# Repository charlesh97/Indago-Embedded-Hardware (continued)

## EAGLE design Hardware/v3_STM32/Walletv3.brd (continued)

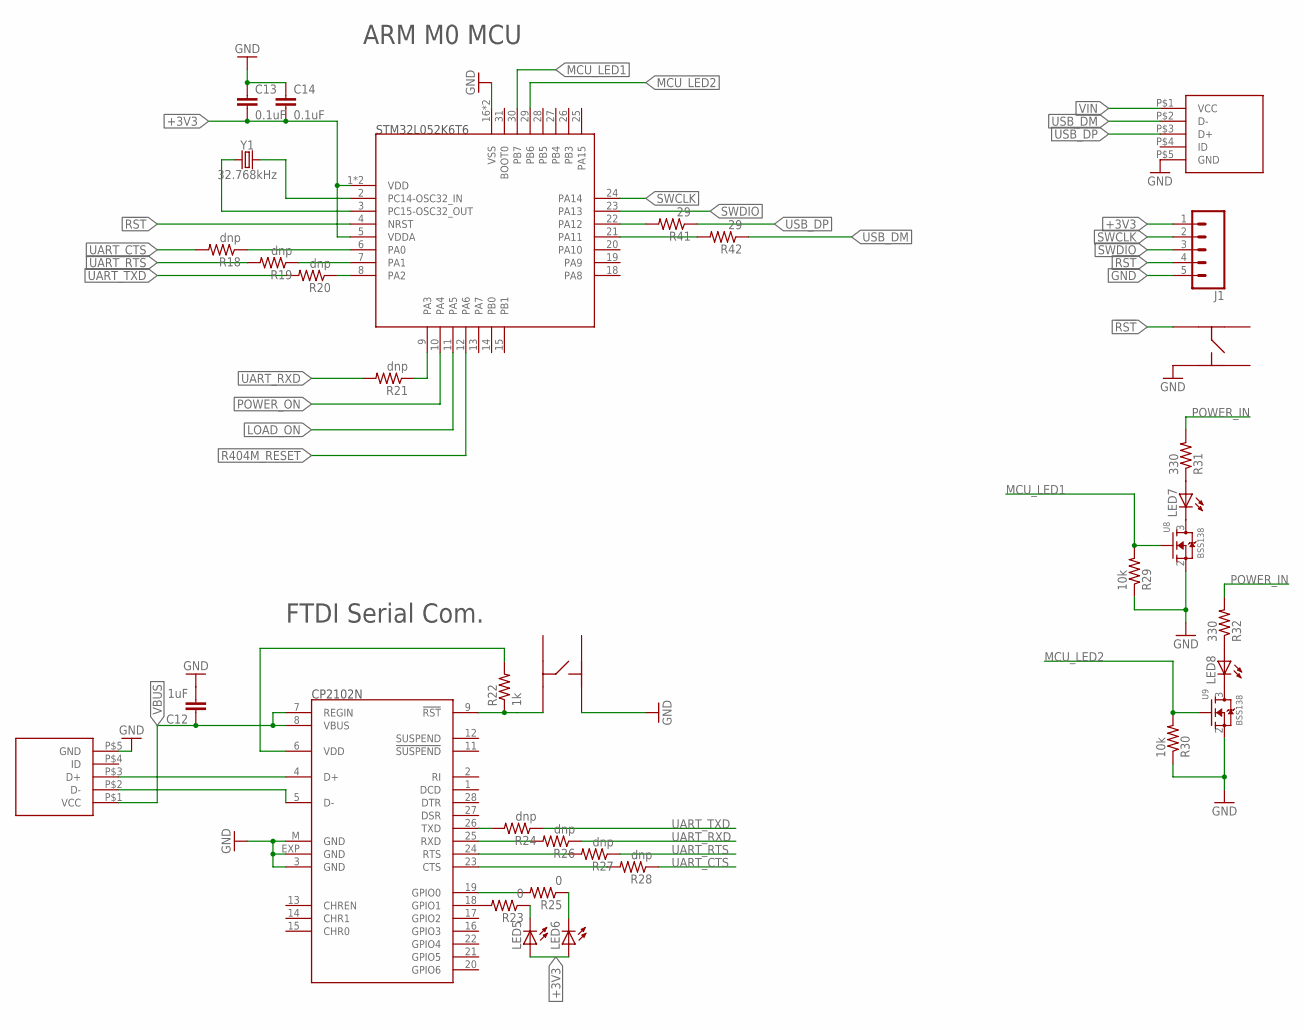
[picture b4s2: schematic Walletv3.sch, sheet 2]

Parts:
C12: 1uF; C0402
C13, C14: 0.1uF; C0402
IC1: CP2102; MLP28
J1: CONN_05; 1X05
LED5, LED6, LED7, LED8: LEDCHIPLED_0603; CHIPLED_0603
R18, R19, R20, R21, R24, R26, R27, R28: dnp; R0402
R22: 1k; R0402
R23, R25: 0; R0402
R29, R30: 10k; R0402
R31, R32: 330; R0402
R41, R42: 29; R0402
S3, S4: KMR731NG
U7: STM32L052K6T6LQFP32-7X7; QFP80P900X900X160-32
U8, U9: BSS138; SOT23-3
U$3, U$4: MICRO_USB; MOLEX_USB
Y1: 32.768kHz; CRYSTAL-SMD-3.2X1.5MM

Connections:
!RST: J1.4, S4.P$1, U7.4 (NRST)
+3V3: C13.2, C14.2, J1.1, LED5.A, LED6.A, U7.1 (VDD), U7.5 (VDDA), U7.17 (VDD); also elsewhere on the board
D_N: IC1.5 (D-), U$3.P$2 (D-)
D_P: IC1.4 (D+), U$3.P$3 (D+)
GND: C12.2, C13.1, C14.1, IC1.3 (GND), IC1.EXP (GND), IC1.M (GND), J1.5, R29.1, R30.1, S3.P$4, S4.P$4, U7.16 (VSS), U7.32 (VSS), U8.2 (S), U9.2 (S), U$3.P$5 (GND), U$4.P$5 (GND); also elsewhere on the board
LOAD_ON: U7.11 (PA5); also elsewhere on the board
MCU_LED1: R29.2, U7.30 (PB7), U8.1 (G)
MCU_LED2: R30.2, U7.29 (PB6), U9.1 (G)
unnamed: LED7.C, U8.3 (D)
unnamed: LED7.A, R31.1
unnamed: LED8.C, U9.3 (D)
unnamed: LED8.A, R32.1
unnamed: IC1.9 (!RST), R22.1, S3.P$1
unnamed: IC1.6 (VDD), R22.2
unnamed: LED6.C, R25.1
unnamed: IC1.18 (GPIO1), R23.2
unnamed: LED5.C, R23.1
unnamed: IC1.19 (GPIO0), R25.2
unnamed: IC1.26 (TXD), R24.2
unnamed: IC1.25 (RXD), R26.2
unnamed: R18.1, U7.6 (PA0)
unnamed: R19.1, U7.7 (PA1)
unnamed: IC1.24 (RTS), R27.2
unnamed: IC1.23 (CTS), R28.2
unnamed: R20.1, U7.8 (PA2)
unnamed: R21.1, U7.9 (PA3)
unnamed: U7.2 (PC14-OSC32_IN), Y1.P$2 (2)
unnamed: U7.3 (PC15-OSC32_OUT), Y1.P$1 (1)
unnamed: R41.2, U7.22 (PA12)
unnamed: R42.2, U7.21 (PA11)
POWER_IN: R31.2, R32.2; also elsewhere on the board
POWER_ON: U7.10 (PA4); also elsewhere on the board
R404M_RESET: U7.12 (PA6); also elsewhere on the board
SWCLK: J1.2, U7.24 (PA14)
SWDIO: J1.3, U7.23 (PA13)
UART_CTS: R18.2, R28.1; also elsewhere on the board
UART_RTS: R19.2, R27.1; also elsewhere on the board
UART_RXD: R21.2, R26.1; also elsewhere on the board
UART_TXD: R20.2, R24.1; also elsewhere on the board
USB_DM: R42.1, U$4.P$2 (D-)
USB_DP: R41.1, U$4.P$3 (D+)
VBUS: C12.1, IC1.7 (REGIN), IC1.8 (VBUS), U$3.P$1 (VCC); also elsewhere on the board
VIN: U$4.P$1 (VCC)

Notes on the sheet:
FTDI Serial Com.
ARM M0 MCU

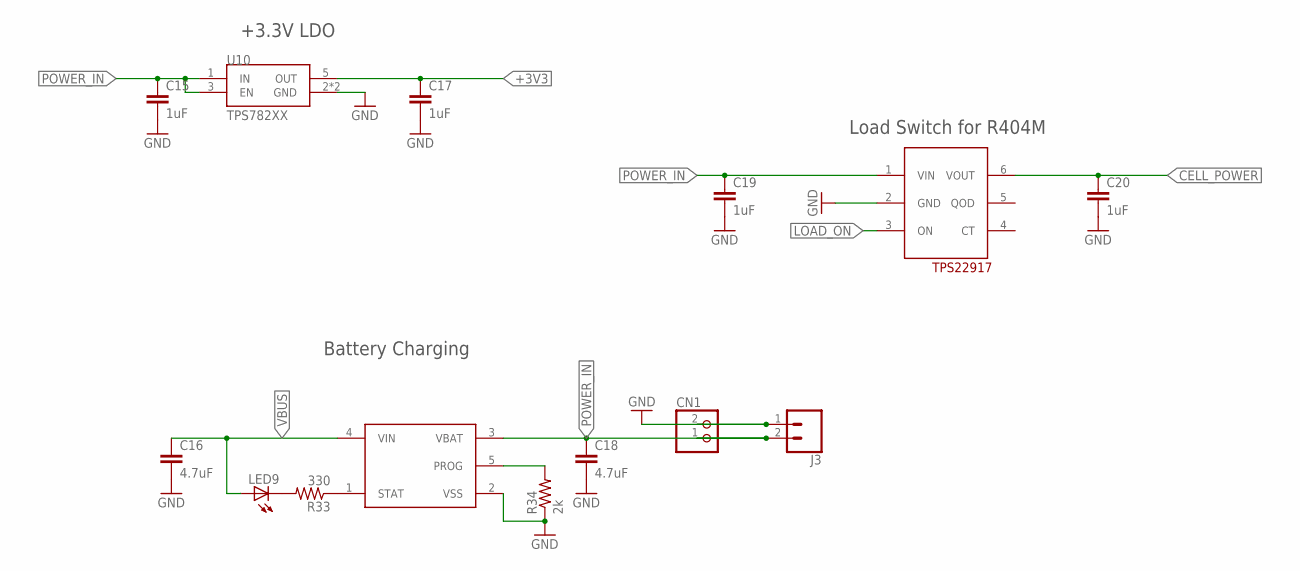
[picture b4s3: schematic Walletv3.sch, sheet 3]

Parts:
C15, C17, C19, C20: 1uF; C0402
C16, C18: 4.7uF; C0603
CN1: JST_2PIN-SMT-RA; JST-PH-2-SMT-RA
J3: CONN_02; 1X02
LED9: LEDCHIP-LED0603; CHIP-LED0603
R33: 330; R0402
R34: 2k; R0402
U10: TPS782XX; SOT23-5L
U11: MCP73831; SOT23-5L
U12: TPS22917; SOT23-6

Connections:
+3V3: C17.1, U10.5 (OUT); also elsewhere on the board
CELL_POWER: C20.1, U12.6 (VOUT); also elsewhere on the board
GND: C15.2, C16.2, C17.2, C18.2, C19.2, C20.2, CN1.2 (1), J3.1, R34.1, U10.2 (GND), U10.4 (GND), U11.2 (VSS), U12.2 (GND); also elsewhere on the board
LOAD_ON: U12.3 (ON); also elsewhere on the board
unnamed: R34.2, U11.5 (PROG)
unnamed: R33.1, U11.1 (STAT)
unnamed: LED9.C, R33.2
POWER_IN: C15.1, C18.1, C19.1, CN1.1 (2), J3.2, U10.1 (IN), U10.3 (EN), U11.3 (VBAT), U12.1 (VIN); also elsewhere on the board
VBUS: C16.1, LED9.A, U11.4 (VIN); also elsewhere on the board

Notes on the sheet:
+3.3V LDO
Load Switch for R404M
Battery Charging

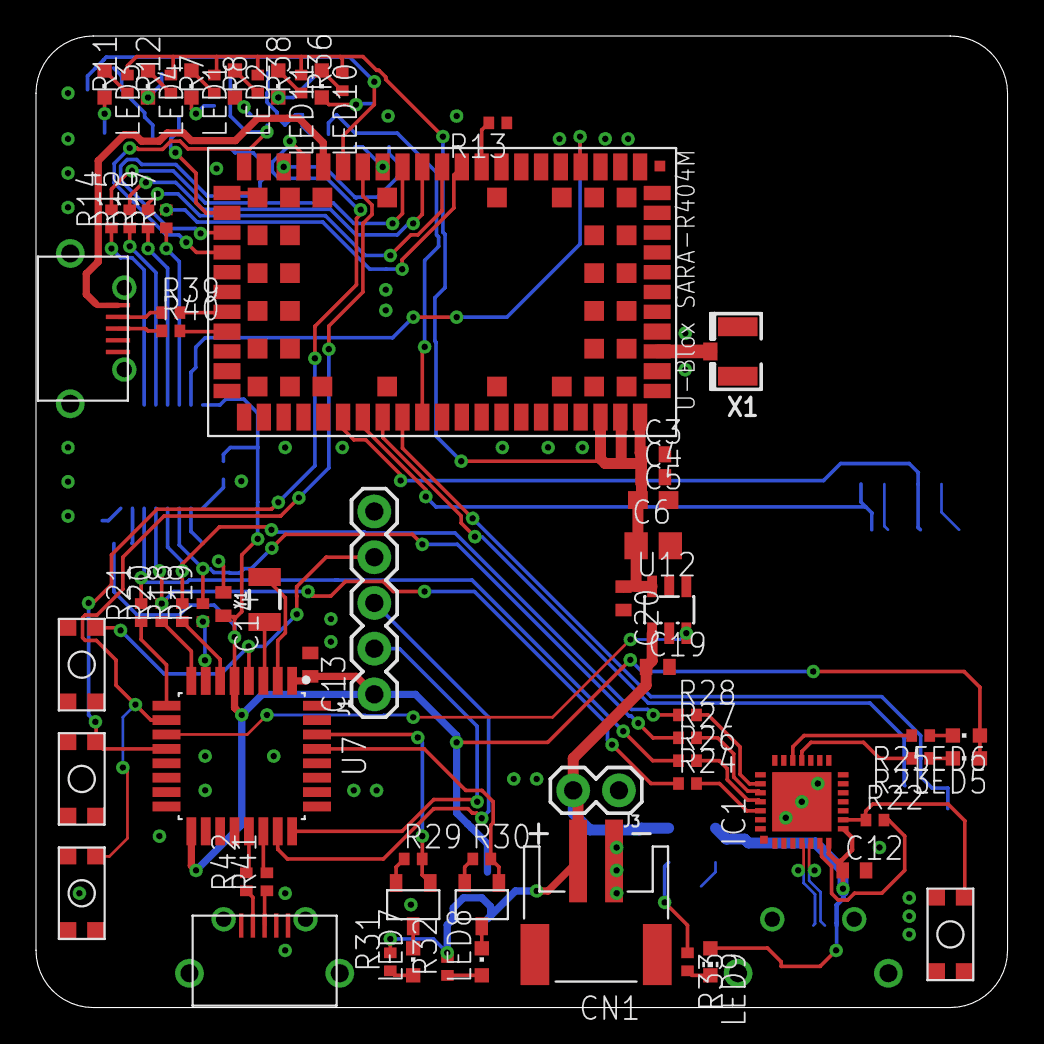
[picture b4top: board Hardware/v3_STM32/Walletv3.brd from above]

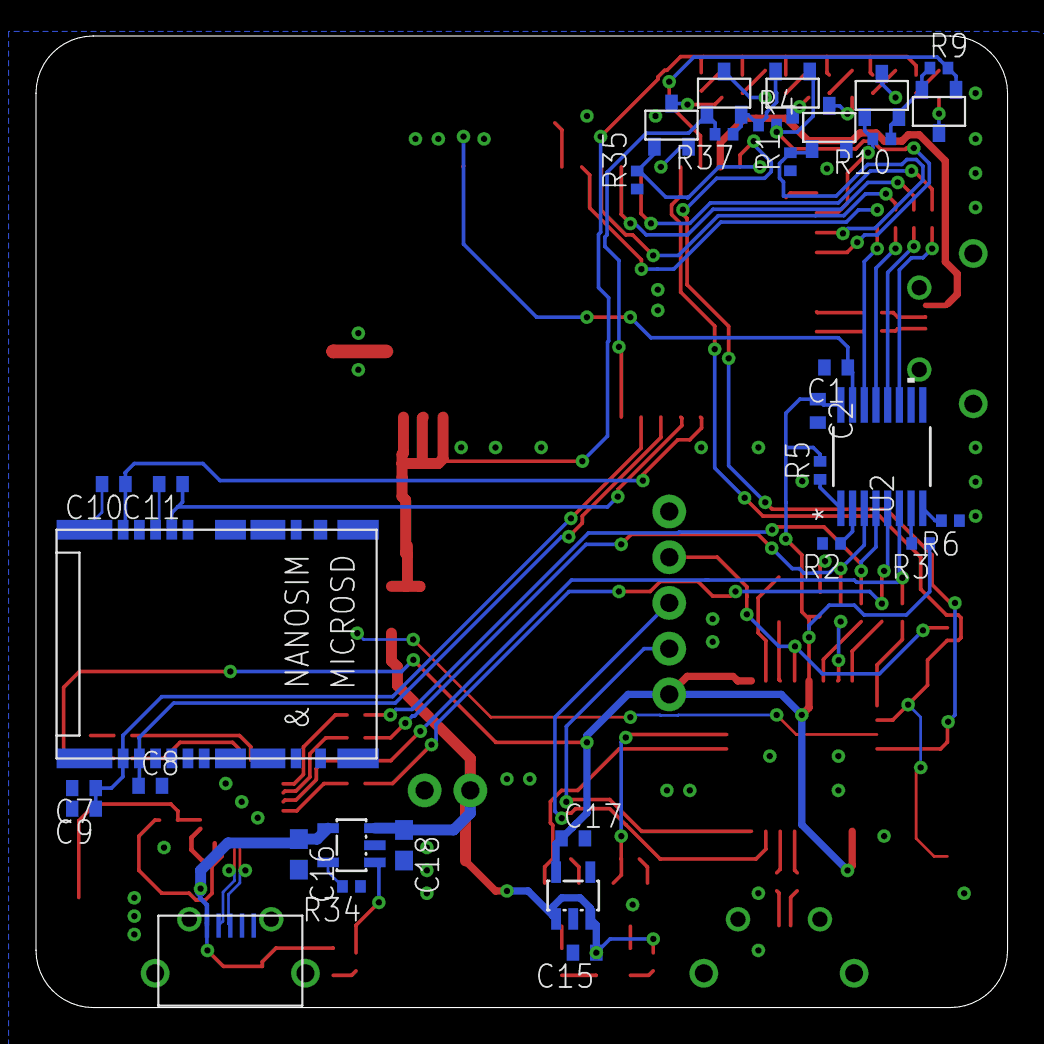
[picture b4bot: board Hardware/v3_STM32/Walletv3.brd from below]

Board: 2 copper layers, 54.0 x 54.0 mm, 101 parts (33 on the bottom side), 88 nets.

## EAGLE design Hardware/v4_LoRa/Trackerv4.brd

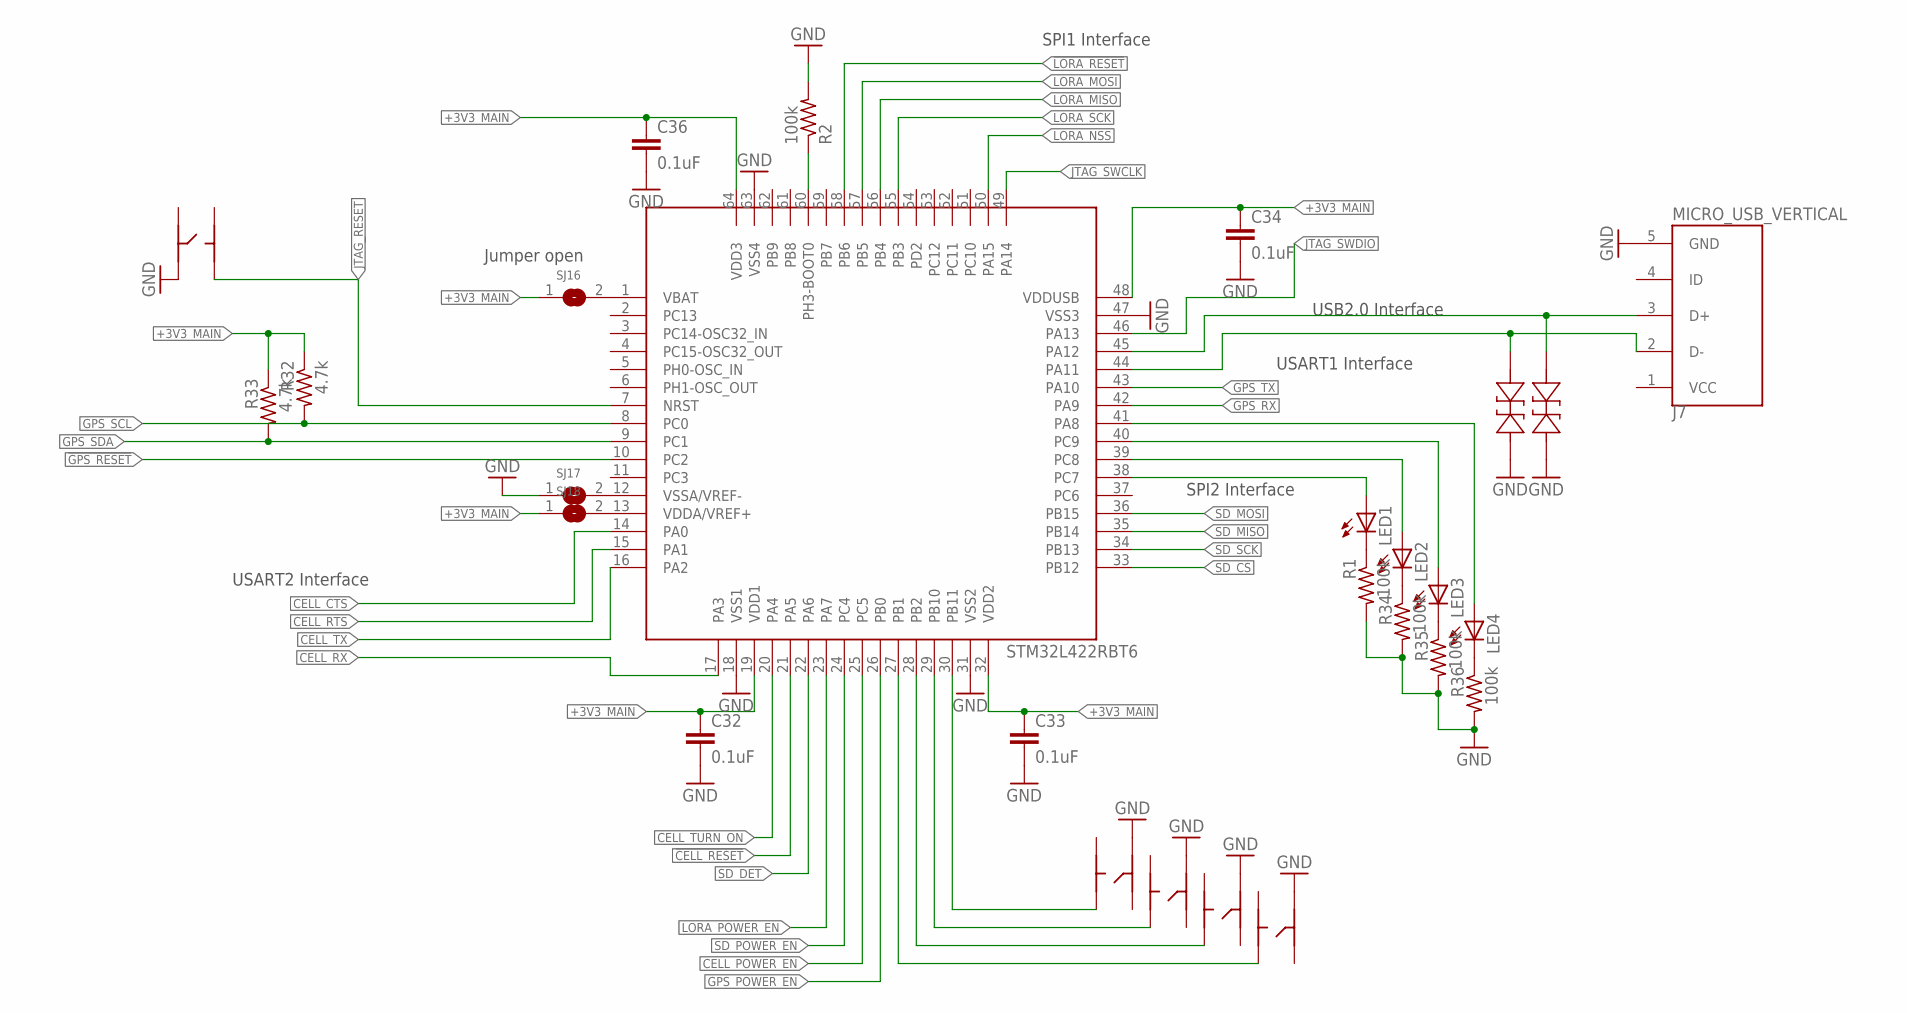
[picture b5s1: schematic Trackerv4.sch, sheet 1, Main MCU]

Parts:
C32, C33, C34, C36: 0.1uF; C0402
CR7, CR8: PESD0402-140; PESD0402
J7: MICRO_USB_VERTICAL
LED1, LED2, LED3, LED4: LEDCHIP-LED0603; CHIP-LED0603
R1, R2, R34, R35, R36: 100k; R0402
R32, R33: 4.7k; R0402
S1, S2, S3, S4, S5: KMR731NG
SJ16, SJ17, SJ18: SOLDERJUMPERREFLOW_NOPASTE; SOLDERJUMPER_REFLOW_NOPASTE
U$1: STM32L422RBT6; QFP50P1200X1200X160-64

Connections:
!CELL_RESET: U$1.21 (PA5); also elsewhere on the board
!GPS_RESET: U$1.10 (PC2); also elsewhere on the board
!LORA_RESET: U$1.58 (PB6); also elsewhere on the board
+3V3_MAIN: C32.1, C33.1, C34.1, C36.1, R32.1, R33.1, SJ16.1, SJ18.1, U$1.19 (VDD1), U$1.32 (VDD2), U$1.48 (VDDUSB), U$1.64 (VDD3); also elsewhere on the board
CELL_CTS: U$1.14 (PA0); also elsewhere on the board
CELL_POWER_EN: U$1.25 (PC5); also elsewhere on the board
CELL_RTS: U$1.15 (PA1); also elsewhere on the board
CELL_RX: U$1.17 (PA3); also elsewhere on the board
CELL_TURN_ON: U$1.20 (PA4); also elsewhere on the board
CELL_TX: U$1.16 (PA2); also elsewhere on the board
GND: C32.2, C33.2, C34.2, C36.2, CR7.1 (11), CR8.1 (11), J7.5 (GND), R1.2, R2.2, R34.2, R35.2, R36.2, S1.P$1, S2.P$1, S3.P$1, S4.P$1, S5.P$1, SJ17.1, U$1.18 (VSS1), U$1.31 (VSS2), U$1.47 (VSS3), U$1.63 (VSS4); also elsewhere on the board
GPS_POWER_EN: U$1.26 (PB0); also elsewhere on the board
GPS_RX: U$1.42 (PA9); also elsewhere on the board
GPS_SCL: R32.2, U$1.8 (PC0); also elsewhere on the board
GPS_SDA: R33.2, U$1.9 (PC1); also elsewhere on the board
GPS_TX: U$1.43 (PA10); also elsewhere on the board
JTAG_RESET: S1.P$4, U$1.7 (NRST); also elsewhere on the board
JTAG_SWCLK: U$1.49 (PA14); also elsewhere on the board
JTAG_SWDIO: U$1.46 (PA13); also elsewhere on the board
LORA_MISO: U$1.56 (PB4); also elsewhere on the board
LORA_MOSI: U$1.57 (PB5); also elsewhere on the board
LORA_NSS: U$1.50 (PA15); also elsewhere on the board
LORA_POWER_EN: U$1.23 (PA7); also elsewhere on the board
LORA_SCK: U$1.55 (PB3); also elsewhere on the board
MCU_USB_N: CR7.2 (22), J7.2 (D-), U$1.44 (PA11)
MCU_USB_P: CR8.2 (22), J7.3 (D+), U$1.45 (PA12)
unnamed: R2.1, U$1.60 (PH3-BOOT0)
unnamed: SJ16.2, U$1.1 (VBAT)
unnamed: SJ17.2, U$1.12 (VSSA/VREF-)
unnamed: SJ18.2, U$1.13 (VDDA/VREF+)
unnamed: S5.P$3, U$1.27 (PB1)
unnamed: S4.P$3, U$1.28 (PB2)
unnamed: S3.P$3, U$1.29 (PB10)
unnamed: S2.P$3, U$1.30 (PB11)
unnamed: LED1.C, R1.1
unnamed: LED2.C, R34.1
unnamed: LED3.C, R35.1
unnamed: LED4.C, R36.1
unnamed: LED1.A, U$1.38 (PC7)
unnamed: LED2.A, U$1.39 (PC8)
unnamed: LED3.A, U$1.40 (PC9)
unnamed: LED4.A, U$1.41 (PA8)
SD_CS: U$1.33 (PB12); also elsewhere on the board
SD_DET: U$1.22 (PA6); also elsewhere on the board
SD_MISO: U$1.35 (PB14); also elsewhere on the board
SD_MOSI: U$1.36 (PB15); also elsewhere on the board
SD_POWER_EN: U$1.24 (PC4); also elsewhere on the board
SD_SCK: U$1.34 (PB13); also elsewhere on the board

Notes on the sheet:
SPI1 Interface
SPI2 Interface
USART2 Interface
USB2.0 Interface
USART1 Interface
Jumper open

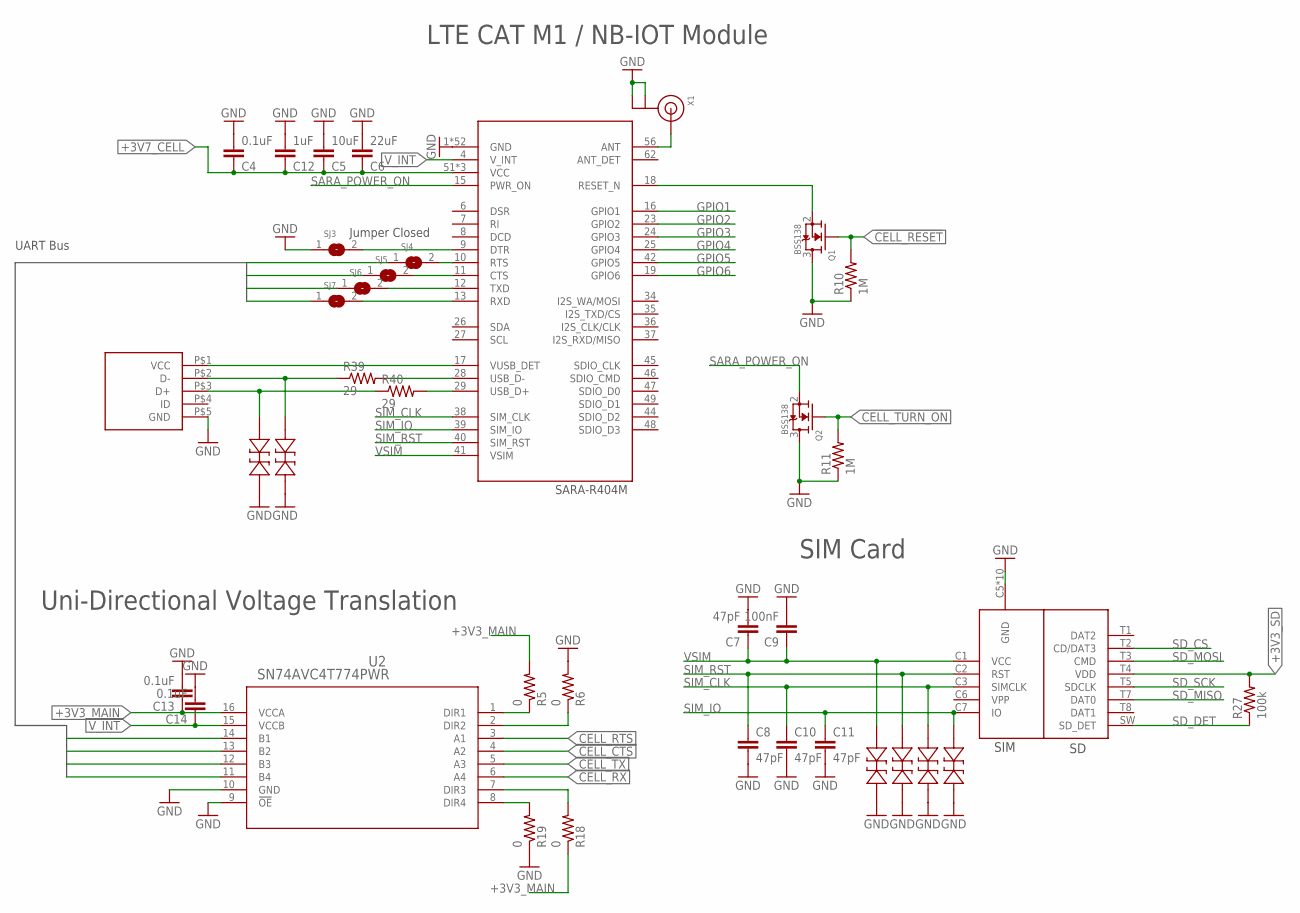
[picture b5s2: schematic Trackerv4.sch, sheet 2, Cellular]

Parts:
C4, C13, C14: 0.1uF; C0402
C5: 10uF; C0603
C6: 22uF; C0805
C7, C8, C10, C11: 47pF; C0402
C9: 100nF; C0402
C12: 1uF; C0402
CR1, CR2, CR3, CR4, CR5, CR6: PESD0402-140; PESD0402
Q1, Q2: BSS138; SOT23-3
R5, R6, R18, R19: 0; R0402
R10, R11: 1M; R0402
R27: 100k; R0402
R39, R40: 29; R0402
SJ3, SJ4, SJ5, SJ6, SJ7: SOLDERJUMPERCLOSED; SOLDERJUMPER_CLOSEDWIRE
U2: SN74AVC4T774PWR; PW16
U6: SARA-R404M
U$5: SIM_SD_MOLEX
U$6: MICRO_USB; MOLEX_USB
X1: ANTENNA_U.FL; U.FL

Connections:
!CELL_RESET: Q1.1 (G), R10.2; also elsewhere on the board
+3V3_MAIN: C13.1, R5.2, R18.1, U2.16 (VCCA); also elsewhere on the board
+3V3_SD: R27.2, U$5.T4 (VDD); also elsewhere on the board
+3V7_CELL: C4.1, C5.1, C6.1, C12.1, U6.51 (VCC), U6.52 (VCC), U6.53 (VCC); also elsewhere on the board
CELL_CTS: U2.4 (A2); also elsewhere on the board
CELL_D_N: CR6.2 (22), R39.1, U$6.P$2 (D-)
CELL_D_P: CR5.2 (22), R40.1, U$6.P$3 (D+)
CELL_RTS: U2.3 (A1); also elsewhere on the board
CELL_RX: U2.6 (A4); also elsewhere on the board
CELL_TURN_ON: Q2.1 (G), R11.2; also elsewhere on the board
CELL_TX: U2.5 (A3); also elsewhere on the board
GND: C4.2, C5.2, C6.2, C7.2, C8.2, C9.2, C10.2, C11.2, C12.2, C13.2, C14.2, CR1.1 (11), CR2.1 (11), CR3.1 (11), CR4.1 (11), CR5.1 (11), CR6.1 (11), Q1.3 (D), Q2.3 (D), R6.2, R10.1, R11.1, R19.1, SJ3.1, U2.9 (!OE), U2.10 (GND), U6.1 (GND), U6.3 (GND), U6.5 (GND), U6.14 (GND), U6.20 (GND), U6.21 (GND), U6.22 (GND), U6.30 (GND), U6.32 (GND), U6.43 (GND), U6.50 (GND), U6.54 (GND), U6.55 (GND), U6.57 (GND), U6.58 (GND), U6.59 (GND), U6.60 (GND), U6.61 (GND), U6.63 (GND), U6.64 (GND), U6.65 (GND), U6.66 (GND), U6.67 (GND), U6.68 (GND), U6.69 (GND), U6.70 (GND), U6.71 (GND), U6.72 (GND), U6.73 (GND), U6.74 (GND), U6.75 (GND), U6.76 (GND), U6.77 (GND), U6.78 (GND), U6.79 (GND), U6.80 (GND), U6.81 (GND), U6.82 (GND), U6.83 (GND), U6.84 (GND), U6.85 (GND), U6.86 (GND), U6.87 (GND), U6.88 (GND), U6.89 (GND), U6.90 (GND), U6.91 (GND), U6.92 (GND), U6.93 (GND), U6.94 (GND), U6.95 (GND), U6.96 (GND), U$5.C5 (GND), U$5.G1 (GND), U$5.G2 (GND), U$5.G3 (GND), U$5.G4 (GND), U$5.G5 (GND), U$5.G6 (GND), U$5.G7 (GND), U$5.G8 (GND), U$5.T6 (GND), U$6.P$5 (GND), X1.1 (GND), X1.2 (GND); also elsewhere on the board
GPIO1: U6.16 (GPIO1); also elsewhere on the board
GPIO2: U6.23 (GPIO2); also elsewhere on the board
GPIO3: U6.24 (GPIO3); also elsewhere on the board
GPIO4: U6.25 (GPIO4); also elsewhere on the board
GPIO5: U6.42 (GPIO5); also elsewhere on the board
GPIO6: U6.19 (GPIO6); also elsewhere on the board
unnamed: U6.17 (VUSB_DET), U$6.P$1 (VCC)
unnamed: SJ6.2, U6.12 (TXD)
unnamed: SJ7.2, U6.13 (RXD)
unnamed: Q1.2 (S), U6.18 (RESET_N)
unnamed: U6.56 (ANT), X1.3 (SIGNAL)
unnamed: SJ3.2, U6.9 (DTR)
unnamed: SJ5.2, U6.11 (CTS)
unnamed: SJ4.2, U6.10 (RTS)
unnamed: R6.1, U2.2 (DIR2)
unnamed: R5.1, U2.1 (DIR1)
unnamed: R18.2, U2.7 (DIR3)
unnamed: R19.2, U2.8 (DIR4)
unnamed: R39.2, U6.28 (USB_D-)
unnamed: R40.2, U6.29 (USB_D+)
SARA_CTS: SJ5.1, U2.13 (B2)
SARA_POWER_ON: Q2.2 (S), U6.15 (PWR_ON)
SARA_RTS: SJ4.1, U2.14 (B1)
SARA_RX: SJ7.1, U2.11 (B4)
SARA_TX: SJ6.1, U2.12 (B3)
SD_CS: U$5.T2 (CD/DAT3); also elsewhere on the board
SD_DET: R27.1, U$5.SW (SD_DET); also elsewhere on the board
SD_MISO: U$5.T7 (DAT0); also elsewhere on the board
SD_MOSI: U$5.T3 (CMD); also elsewhere on the board
SD_SCK: U$5.T5 (SDCLK); also elsewhere on the board
SIM_CLK: C10.1, CR3.2 (22), U6.38 (SIM_CLK), U$5.C3 (SIMCLK)
SIM_IO: C11.1, CR4.2 (22), U6.39 (SIM_IO), U$5.C7 (IO)
SIM_RST: C8.1, CR2.2 (22), U6.40 (SIM_RST), U$5.C2 (RST)
VSIM: C7.1, C9.1, CR1.2 (22), U6.41 (VSIM), U$5.C1 (VCC)
V_INT: C14.1, U2.15 (VCCB), U6.4 (V_INT)

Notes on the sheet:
Uni-Directional Voltage Translation
LTE CAT M1 / NB-IOT Module
SIM Card
Jumper Closed
UART Bus

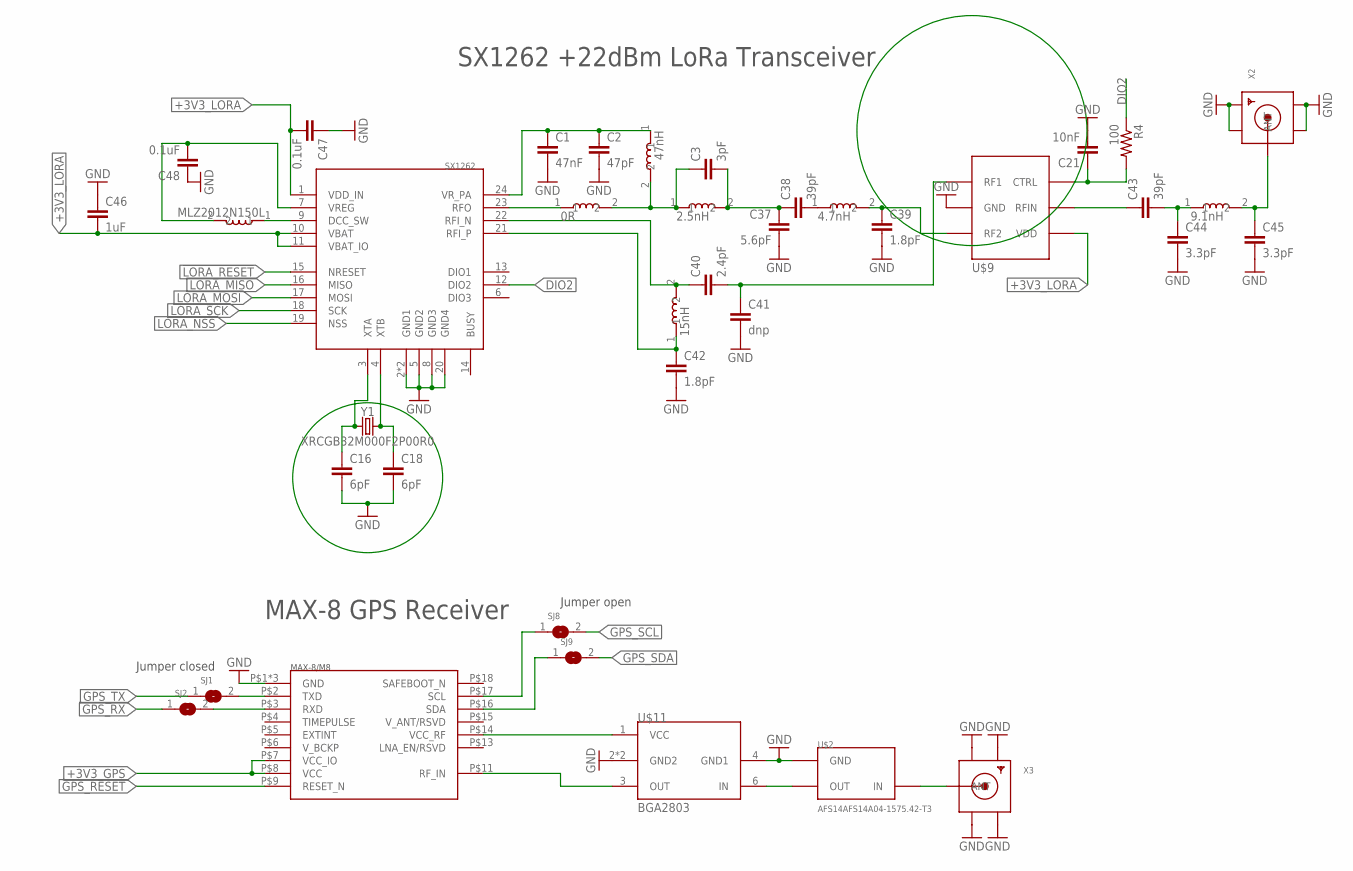
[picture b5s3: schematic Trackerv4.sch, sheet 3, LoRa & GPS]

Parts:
C1: 47nF; C0402
C2: 47pF; C0402
C3: 3pF; C0402
C16, C18: 6pF; C0402
C21: 10nF; C0402
C37: 5.6pF; C0402
C38, C43: 39pF; C0402
C39, C42: 1.8pF; C0402
C40: 2.4pF; C0402
C41: dnp; C0402
C44, C45: 3.3pF; C0402
C46: 1uF; C0603
C47, C48: 0.1uF; C0402
R4: 100; R0402
SJ1, SJ2: SOLDERJUMPERCLOSED; SOLDERJUMPER_CLOSEDWIRE
SJ8, SJ9: SOLDERJUMPERREFLOW; SOLDERJUMPER_REFLOW
U$2: AFS14AFS14A04-1575.42-T3; AFS14
U$3: MLZ2012N150L; C0805
U$7: SX1262; QFN50P400X400X100-25T260
U$8: MAX-8/M8; MAX-8-M8
U$9: BGS12SN6E6327XTSA1; TSNP-6-8
U$10: 47nH; 0402
U$11: BGA2803; SOT363_6SOIC
U$12: 2.5nH; 0402
U$13: 4.7nH; 0402
U$14: 15nH; 0402
U$15: 9.1nH; 0402
U$16: 0R; 0402
X2: SMACONNECTOR_EDGE; SMA_EDGELAUNCH
X3: SMACONNECTOR_EDGE_UFL; SMA_EDGELAUNCH_UFL
Y1: XRCGB32M000F2P00R0; CRYSTAL-SMD-2.0X1.6MM

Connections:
!GPS_RESET: U$8.P$9 (RESET_N); also elsewhere on the board
!LORA_RESET: U$7.15 (NRESET); also elsewhere on the board
+3V3_GPS: U$8.P$7 (VCC_IO), U$8.P$8 (VCC); also elsewhere on the board
+3V3_LORA: C46.2, C47.2, U$7.1 (VDD_IN), U$7.10 (VBAT), U$7.11 (VBAT_IO), U$9.P$6 (VDD); also elsewhere on the board
DIO2: R4.1, U$7.12 (DIO2)
GND: C1.2, C2.2, C16.2, C18.2, C21.2, C37.2, C39.2, C41.2, C42.2, C44.2, C45.2, C46.1, C47.1, C48.1, U$2.P$2 (GND), U$2.P$3 (GND), U$2.P$5 (GND), U$7.2 (GND1), U$7.5 (GND2), U$7.8 (GND3), U$7.20 (GND4), U$7.25 (GND1), U$8.P$1 (GND), U$8.P$10 (GND), U$8.P$12 (GND), U$9.P$2 (GND), U$11.2 (GND2), U$11.4 (GND1), U$11.5 (GND2), X2.GND@1 (GND4), X2.GND@2 (GND3), X2.GND@3 (GND2), X2.GND@4 (GND1), X3.GND@1 (GND1), X3.GND@2 (GND2), X3.GND@3 (GND3), X3.GND@4 (GND4); also elsewhere on the board
GPS_RX: SJ2.1; also elsewhere on the board
GPS_SCL: SJ8.2; also elsewhere on the board
GPS_SDA: SJ9.2; also elsewhere on the board
GPS_TX: SJ1.1; also elsewhere on the board
LORA_MISO: U$7.16 (MISO); also elsewhere on the board
LORA_MOSI: U$7.17 (MOSI); also elsewhere on the board
LORA_NSS: U$7.19 (NSS); also elsewhere on the board
LORA_SCK: U$7.18 (SCK); also elsewhere on the board
unnamed: SJ1.2, U$8.P$2 (TXD)
unnamed: SJ2.2, U$8.P$3 (RXD)
unnamed: U$3.1, U$7.9 (DCC_SW)
unnamed: C16.1, U$7.3 (XTA), Y1.1
unnamed: C18.1, U$7.4 (XTB), Y1.3 (2)
unnamed: C48.2, U$3.2, U$7.7 (VREG)
unnamed: C21.1, R4.2, U$9.P$4 (CTRL)
unnamed: U$8.P$11 (RF_IN), U$11.3 (OUT)
unnamed: U$2.P$4 (OUT), U$11.6 (IN)
unnamed: SJ8.1, U$8.P$17 (SCL)
unnamed: SJ9.1, U$8.P$16 (SDA)
unnamed: U$8.P$14 (VCC_RF), U$11.1 (VCC)
unnamed: U$2.P$1 (IN), X3.P (ANT)
unnamed: C39.1, U$9.P$1 (RF2), U$13.2
unnamed: C42.1, U$7.21 (RFI_P), U$14.1
unnamed: C1.1, C2.1, U$7.24 (VR_PA), U$10.1
unnamed: C3.1, U$10.2, U$12.1, U$16.2
unnamed: C3.2, C37.1, C38.1, U$12.2
unnamed: C40.1, U$7.22 (RFI_N), U$14.2
unnamed: C40.2, C41.1, U$9.P$3 (RF1)
unnamed: C38.2, U$13.1
unnamed: C43.2, C44.1, U$15.1
unnamed: C45.1, U$15.2, X2.P (ANT)
unnamed: C43.1, U$9.P$5 (RFIN)
unnamed: U$7.23 (RFO), U$16.1

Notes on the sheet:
SX1262 +22dBm LoRa Transceiver
MAX-8 GPS Receiver
Jumper closed
Jumper open

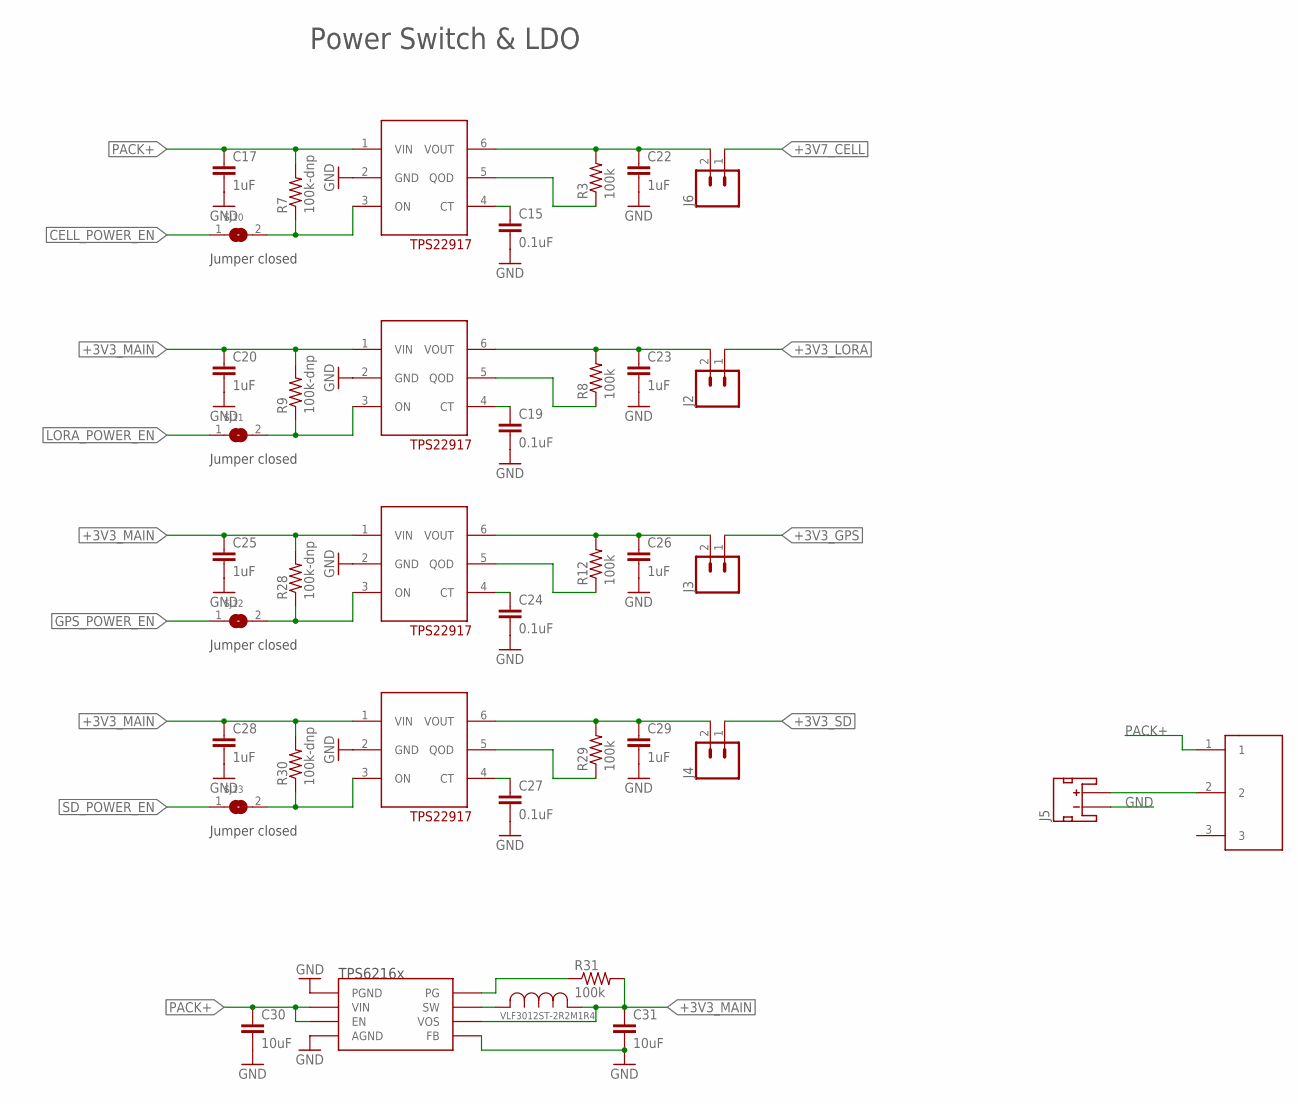
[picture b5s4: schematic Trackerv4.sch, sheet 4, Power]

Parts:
C15, C19, C24, C27: 0.1uF; C0402
C17, C20, C22, C23, C25, C26, C28, C29: 1uF; C0402
C30, C31: 10uF; C0805
J2, J3, J4, J6: CONN_02; 1X02
J5: JST_2MM_MALE; JST-2-SMD
R3, R8, R12, R29, R31: 100k; R0402
R7, R9, R28, R30: 100k-dnp; R0402
SJ10, SJ11, SJ12, SJ13: SOLDERJUMPERCLOSED; SOLDERJUMPER_CLOSEDWIRE
U1, U3, U4, U5: TPS22917; SOT23-6
U14: TPS6216X; 8WSON
U$4: VLF3012ST-2R2M1R4; IND_3010
U$17: SPDT_THRU

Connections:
+3V3_GPS: J3.1; also elsewhere on the board
+3V3_LORA: J2.1; also elsewhere on the board
+3V3_MAIN: C20.1, C25.1, C28.1, C31.1, R9.2, R28.2, R30.2, R31.2, U3.1 (VIN), U4.1 (VIN), U5.1 (VIN), U14.P$6 (VOS), U$4.1; also elsewhere on the board
+3V3_SD: J4.1; also elsewhere on the board
+3V7_CELL: J6.1; also elsewhere on the board
CELL_POWER_EN: SJ10.1; also elsewhere on the board
GND: C15.2, C17.2, C19.2, C20.2, C22.2, C23.2, C24.2, C25.2, C26.2, C27.2, C28.2, C29.2, C30.2, C31.2, J5.1 (-), U1.2 (GND), U3.2 (GND), U4.2 (GND), U5.2 (GND), U14.P$1 (PGND), U14.P$4 (AGND), U14.P$5 (FB), U14.P$9 (AGND); also elsewhere on the board
GPS_POWER_EN: SJ12.1; also elsewhere on the board
LORA_POWER_EN: SJ11.1; also elsewhere on the board
unnamed: C15.1, U1.4 (CT)
unnamed: R3.1, U1.5 (QOD)
unnamed: C19.1, U3.4 (CT)
unnamed: R8.1, U3.5 (QOD)
unnamed: R7.1, SJ10.2, U1.3 (ON)
unnamed: R9.1, SJ11.2, U3.3 (ON)
unnamed: C22.1, J6.2, R3.2, U1.6 (VOUT)
unnamed: C23.1, J2.2, R8.2, U3.6 (VOUT)
unnamed: C24.1, U4.4 (CT)
unnamed: R12.1, U4.5 (QOD)
unnamed: R28.1, SJ12.2, U4.3 (ON)
unnamed: C26.1, J3.2, R12.2, U4.6 (VOUT)
unnamed: C27.1, U5.4 (CT)
unnamed: R29.1, U5.5 (QOD)
unnamed: R30.1, SJ13.2, U5.3 (ON)
unnamed: C29.1, J4.2, R29.2, U5.6 (VOUT)
unnamed: J5.2 (+), U$17.2
unnamed: R31.1, U14.P$8 (PG)
unnamed: U14.P$7 (SW), U$4.2
PACK+: C17.1, C30.1, R7.2, U1.1 (VIN), U14.P$2 (VIN), U14.P$3 (EN), U$17.1
SD_POWER_EN: SJ13.1; also elsewhere on the board

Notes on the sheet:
Power Switch & LDO
Jumper closed

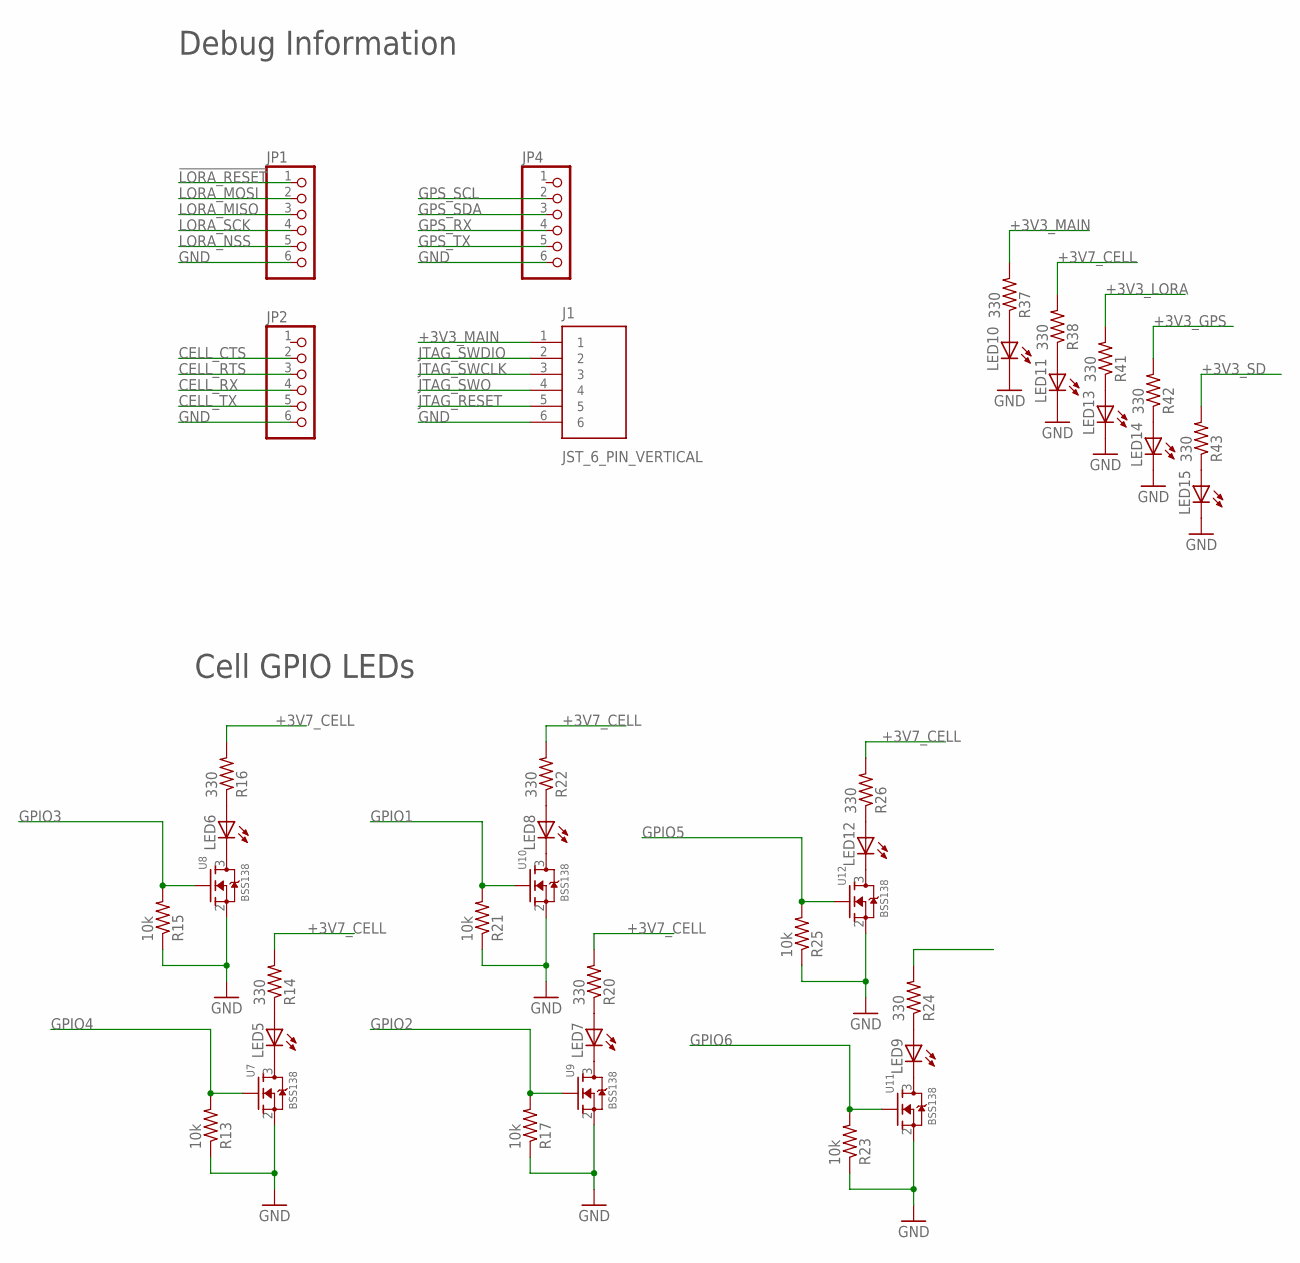
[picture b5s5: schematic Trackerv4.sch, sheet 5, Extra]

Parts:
J1: JST_6_PIN_VERTICAL; JST-6-SMD-VERT-1.0MM
JP1, JP2, JP4: PINHD-1X6; 1X06
LED5, LED6, LED7, LED8, LED9, LED10, LED11, LED12, LED13, LED14, LED15: LEDCHIPLED_0603; CHIPLED_0603
R13, R15, R17, R21, R23, R25: 10k; R0402
R14, R16, R20, R22, R24, R26, R37, R38, R41, R42, R43: 330; R0402
U7, U8, U9, U10, U11, U12: BSS138; SOT23-3

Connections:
!LORA_RESET: JP1.1; also elsewhere on the board
+3V3_GPS: R42.2; also elsewhere on the board
+3V3_LORA: R41.2; also elsewhere on the board
+3V3_MAIN: J1.1, R37.2; also elsewhere on the board
+3V3_SD: R43.2; also elsewhere on the board
+3V7_CELL: R14.2, R16.2, R20.2, R22.2, R24.2, R26.2, R38.2; also elsewhere on the board
CELL_CTS: JP2.2; also elsewhere on the board
CELL_RTS: JP2.3; also elsewhere on the board
CELL_RX: JP2.4; also elsewhere on the board
CELL_TX: JP2.5; also elsewhere on the board
GND: J1.6, JP1.6, JP2.6, JP4.6, LED10.C, LED11.C, LED13.C, LED14.C, LED15.C, R13.1, R15.1, R17.1, R21.1, R23.1, R25.1, U7.2 (S), U8.2 (S), U9.2 (S), U10.2 (S), U11.2 (S), U12.2 (S); also elsewhere on the board
GPIO1: R21.2, U10.1 (G); also elsewhere on the board
GPIO2: R17.2, U9.1 (G); also elsewhere on the board
GPIO3: R15.2, U8.1 (G); also elsewhere on the board
GPIO4: R13.2, U7.1 (G); also elsewhere on the board
GPIO5: R25.2, U12.1 (G); also elsewhere on the board
GPIO6: R23.2, U11.1 (G); also elsewhere on the board
GPS_RX: JP4.4; also elsewhere on the board
GPS_SCL: JP4.2; also elsewhere on the board
GPS_SDA: JP4.3; also elsewhere on the board
GPS_TX: JP4.5; also elsewhere on the board
JTAG_RESET: J1.5; also elsewhere on the board
JTAG_SWCLK: J1.3; also elsewhere on the board
JTAG_SWDIO: J1.2; also elsewhere on the board
JTAG_SWO: J1.4
LORA_MISO: JP1.3; also elsewhere on the board
LORA_MOSI: JP1.2; also elsewhere on the board
LORA_NSS: JP1.5; also elsewhere on the board
LORA_SCK: JP1.4; also elsewhere on the board
unnamed: LED5.C, U7.3 (D)
unnamed: LED5.A, R14.1
unnamed: LED6.C, U8.3 (D)
unnamed: LED6.A, R16.1
unnamed: LED7.C, U9.3 (D)
unnamed: LED7.A, R20.1
unnamed: LED8.C, U10.3 (D)
unnamed: LED8.A, R22.1
unnamed: LED9.C, U11.3 (D)
unnamed: LED9.A, R24.1
unnamed: LED12.C, U12.3 (D)
unnamed: LED12.A, R26.1
unnamed: LED10.A, R37.1
unnamed: LED11.A, R38.1
unnamed: LED13.A, R41.1
unnamed: LED14.A, R42.1
unnamed: LED15.A, R43.1

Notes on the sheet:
Cell GPIO LEDs
Debug Information
